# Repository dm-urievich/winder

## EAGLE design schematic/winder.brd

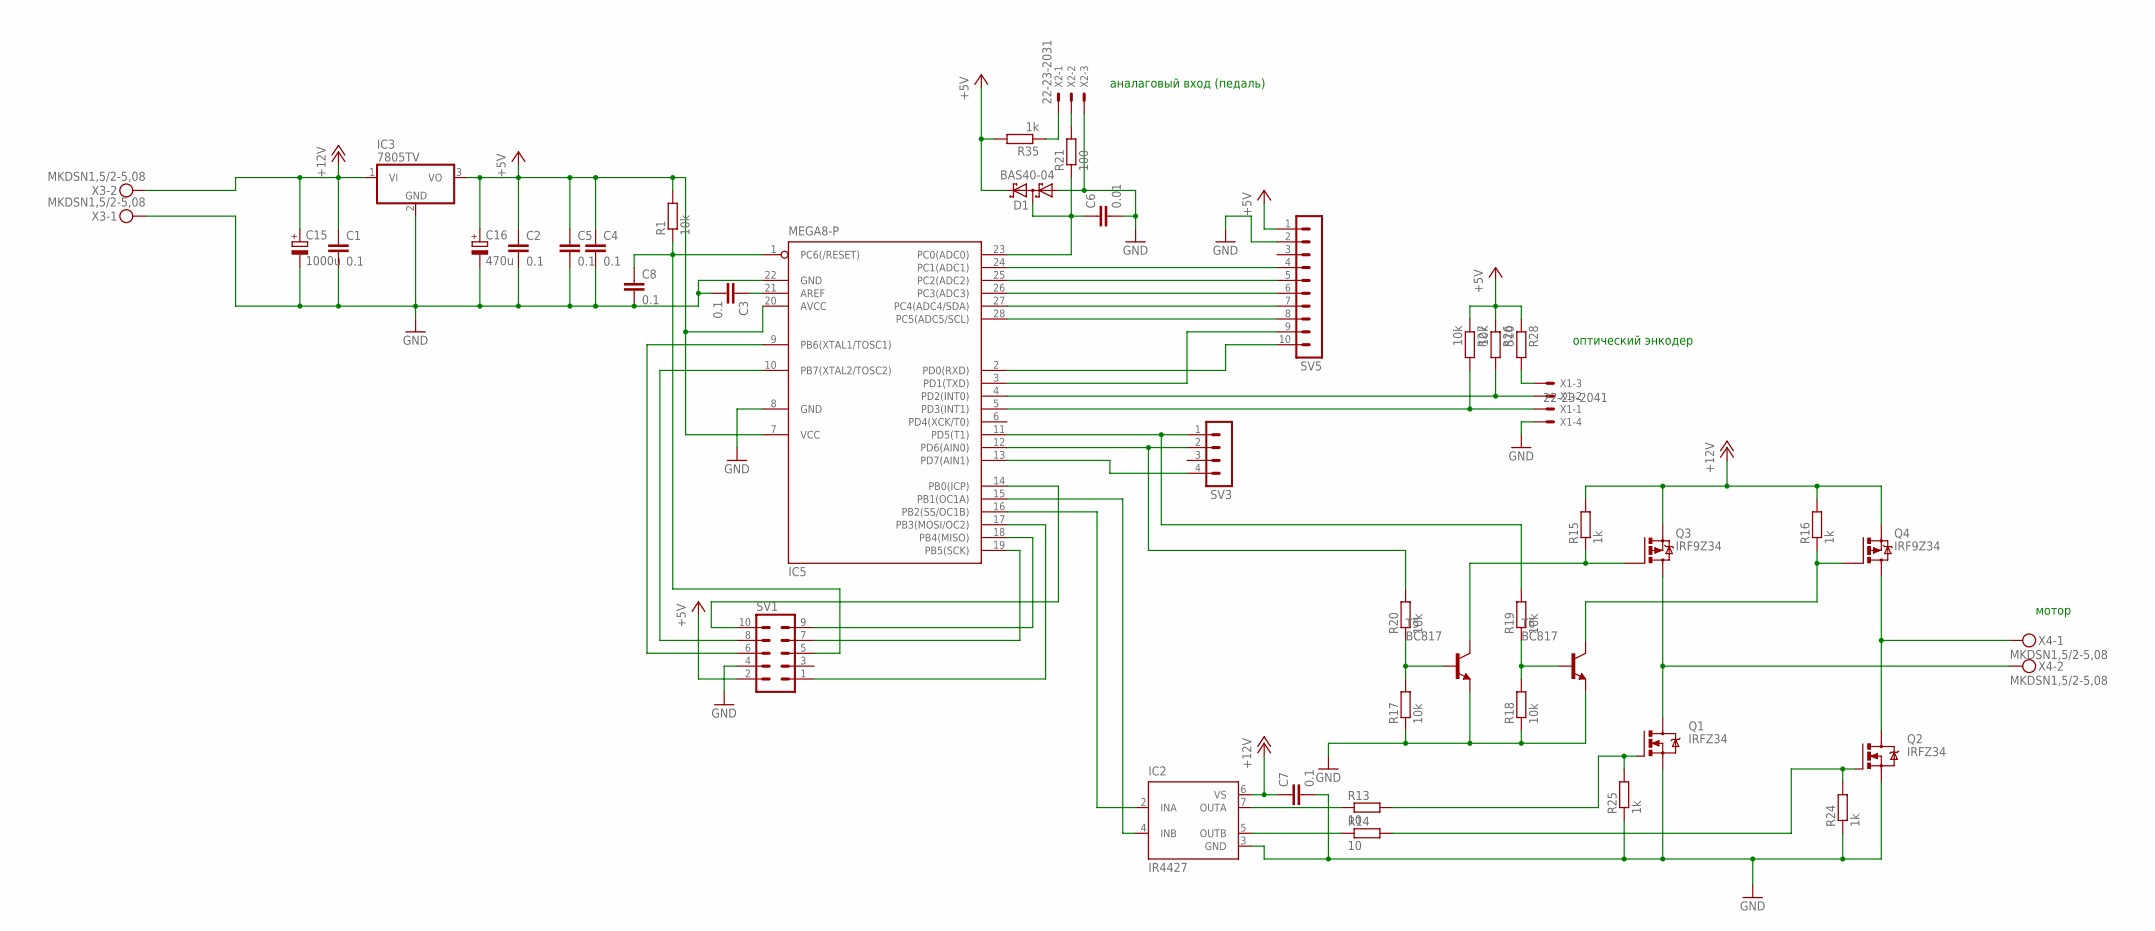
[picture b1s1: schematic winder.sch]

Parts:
C1, C2, C3, C4, C5, C7, C8: 0.1; C0805
C6: 0.01; C0805
C15: 1000u; E3,5-10
C16: 470u; E3,5-10
D1: BAS40-04; SOT23
IC2: IR4427; DIL08
IC3: 7805TV; TO220V
IC5: MEGA8-P; DIL28-3
Q1, Q2: IRFZ34; TO220BV
Q3, Q4: IRF9Z34; TO220BV
R1, R17, R18, R19, R20, R26, R27: 10k; R0805
R13, R14: 10; R0805
R15, R16, R24, R25, R35: 1k; R0805
R21: 100; R0805
R28: 510; R0805
SV1: ML10
SV3: MA04-1
SV5: MA10-1
T5, T6: BC817; SOT23-BEC
X1: 22-23-2041
X2: 22-23-2031
X3, X4: MKDSN1,5/2-5,08

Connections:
+5V: C2.1, C4.1, C5.1, C16.+, D1.2 (C2), IC3.3 (VO), IC5.7 (VCC), IC5.20 (AVCC), R1.2, R26.1, R27.1, R28.1, R35.2, SV1.2, SV5.1
+12V: C1.1, C7.1, C15.+, IC2.6 (VS), IC3.1 (VI), Q3.S, Q4.S, R15.2, R16.2, X3.2
GND: C1.2, C2.2, C3.2, C4.2, C5.2, C6.2, C7.2, C8.2, C15.-, C16.-, D1.1 (A1), IC2.3 (GND), IC3.2 (GND), IC5.8 (GND), IC5.22 (GND), Q1.S, Q2.S, R17.1, R18.1, R24.1, R25.1, SV1.4, SV5.2, T5.E, T6.E, X1.4, X2.3, X3.1
unnamed: IC5.13 (PD7(AIN1)), SV3.4
unnamed: R28.2, X1.3
unnamed: C6.1, D1.3 (C1A2), IC5.23 (PC0(ADC0)), R21.1
unnamed: IC5.14 (PB0(ICP)), SV1.10
unnamed: IC5.5 (PD3(INT1)), R27.2, X1.1
unnamed: IC5.4 (PD2(INT0)), R26.2, X1.2
unnamed: IC5.28 (PC5(ADC5/SCL)), SV5.8
unnamed: IC5.27 (PC4(ADC4/SDA)), SV5.7
unnamed: Q4.G, R16.1, T6.C
unnamed: Q3.G, R15.1, T5.C
unnamed: R17.2, R20.1, T5.B
unnamed: R18.2, R19.1, T6.B
unnamed: R21.2, X2.2
unnamed: Q1.D, Q3.D, X4.2
unnamed: Q2.D, Q4.D, X4.1
unnamed: Q1.G, R13.2, R25.2
unnamed: Q2.G, R14.2, R24.2
unnamed: IC2.7 (OUTA), R13.1
unnamed: IC2.5 (OUTB), R14.1
unnamed: IC2.4 (INB), IC5.15 (PB1(OC1A))
unnamed: IC5.10 (PB7(XTAL2/TOSC2)), SV1.8
unnamed: IC5.17 (PB3(MOSI/OC2)), SV1.1
unnamed: C8.1, IC5.1 (PC6(/RESET)), R1.1, SV1.5
unnamed: R35.1, X2.1
unnamed: IC5.19 (PB5(SCK)), SV1.7
unnamed: IC5.18 (PB4(MISO)), SV1.9
unnamed: C3.1, IC5.21 (AREF)
unnamed: IC5.11 (PD5(T1)), R19.2, SV3.1
unnamed: IC5.12 (PD6(AIN0)), R20.2, SV3.2
unnamed: IC5.26 (PC3(ADC3)), SV5.6
unnamed: IC5.25 (PC2(ADC2)), SV5.5
unnamed: IC5.3 (PD1(TXD)), SV5.9
unnamed: IC5.9 (PB6(XTAL1/TOSC1)), SV1.6
unnamed: IC5.2 (PD0(RXD)), SV5.10
unnamed: IC5.24 (PC1(ADC1)), SV5.4
unnamed: IC2.2 (INA), IC5.16 (PB2(SS/OC1B))

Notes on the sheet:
оптический энкодер
аналаговый вход (педаль)
мотор

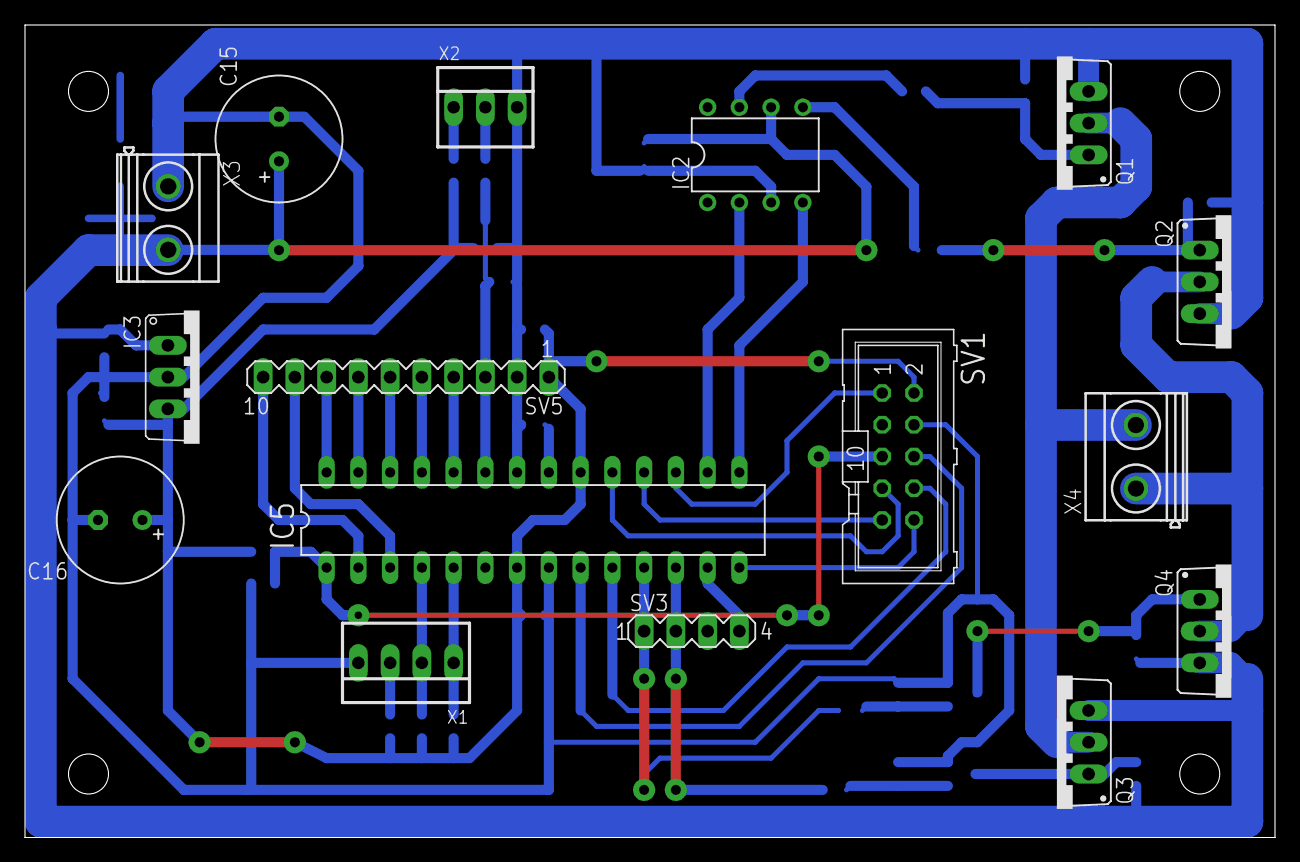
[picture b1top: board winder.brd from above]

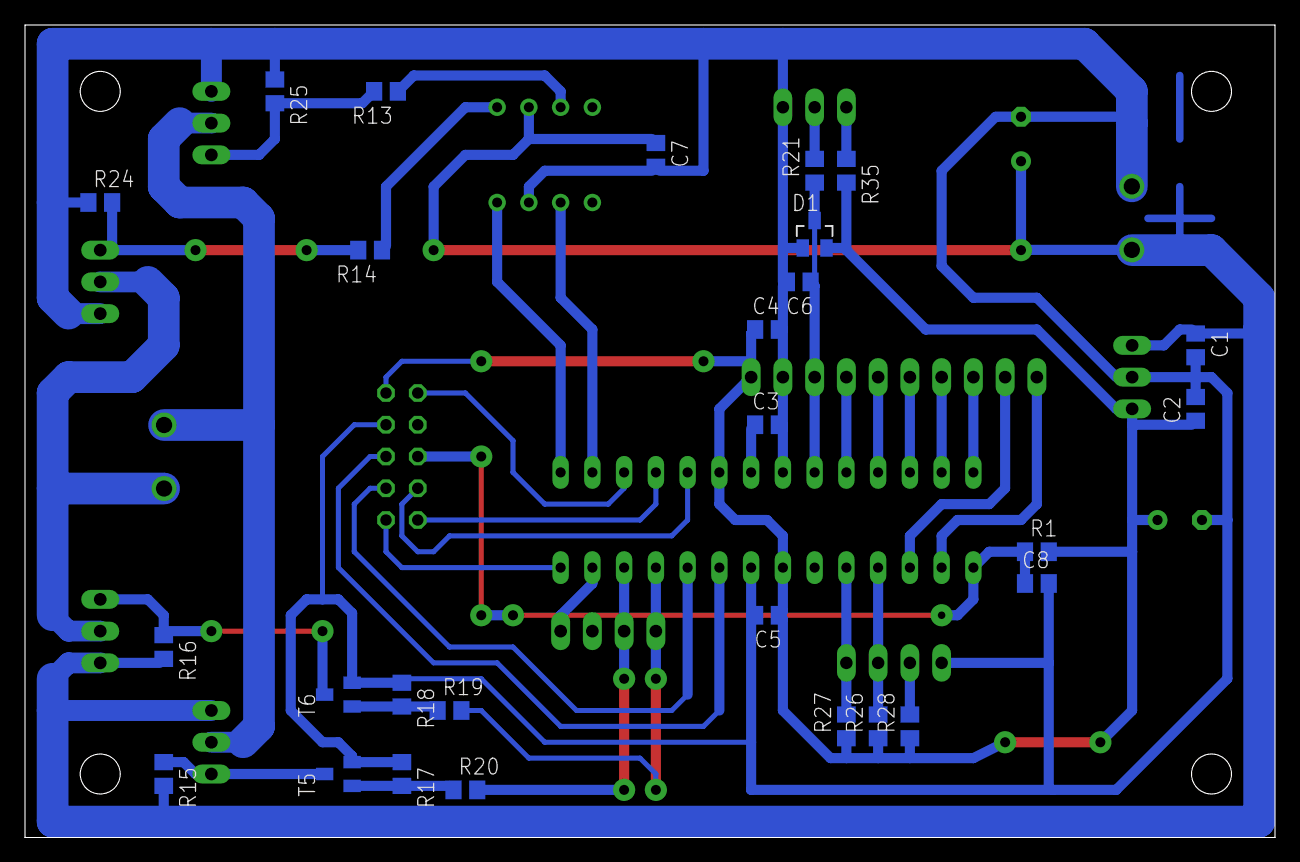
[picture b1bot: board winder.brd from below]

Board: 2 copper layers, 100.0 x 65.0 mm, 43 parts (27 on the bottom side), 39 nets.

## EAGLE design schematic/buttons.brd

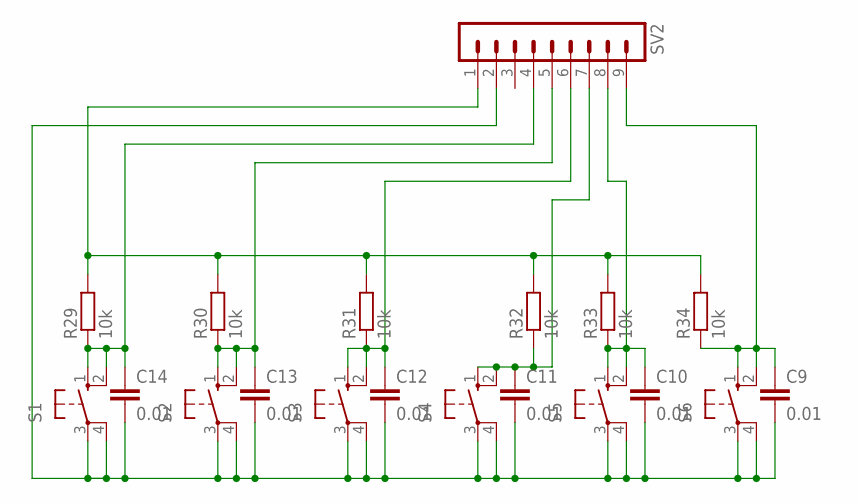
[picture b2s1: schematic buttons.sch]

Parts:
C9, C10, C11, C12, C13, C14: 0.01; C0805
R29, R30, R31, R32, R33, R34: 10k; R0805
S1, S2, S3, S4, S5, S6: 40-XX; B3F-40XX
SV2: MA09-1

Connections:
unnamed: C13.1, R30.1, S2.1 (S), S2.2 (S1), SV2.5
unnamed: C11.1, R32.1, S4.1 (S), S4.2 (S1), SV2.7
unnamed: C10.1, R33.1, S5.1 (S), S5.2 (S1), SV2.8
unnamed: C14.1, R29.1, S1.1 (S), S1.2 (S1), SV2.4
unnamed: C9.1, R34.1, S6.1 (S), S6.2 (S1), SV2.9
unnamed: R29.2, R30.2, R31.2, R32.2, R33.2, R34.2, SV2.1
unnamed: C9.2, C10.2, C11.2, C12.2, C13.2, C14.2, S1.3, S1.4 (P1), S2.3, S2.4 (P1), S3.3, S3.4 (P1), S4.3, S4.4 (P1), S5.3, S5.4 (P1), S6.3, S6.4 (P1), SV2.2
unnamed: C12.1, R31.1, S3.1 (S), S3.2 (S1), SV2.6

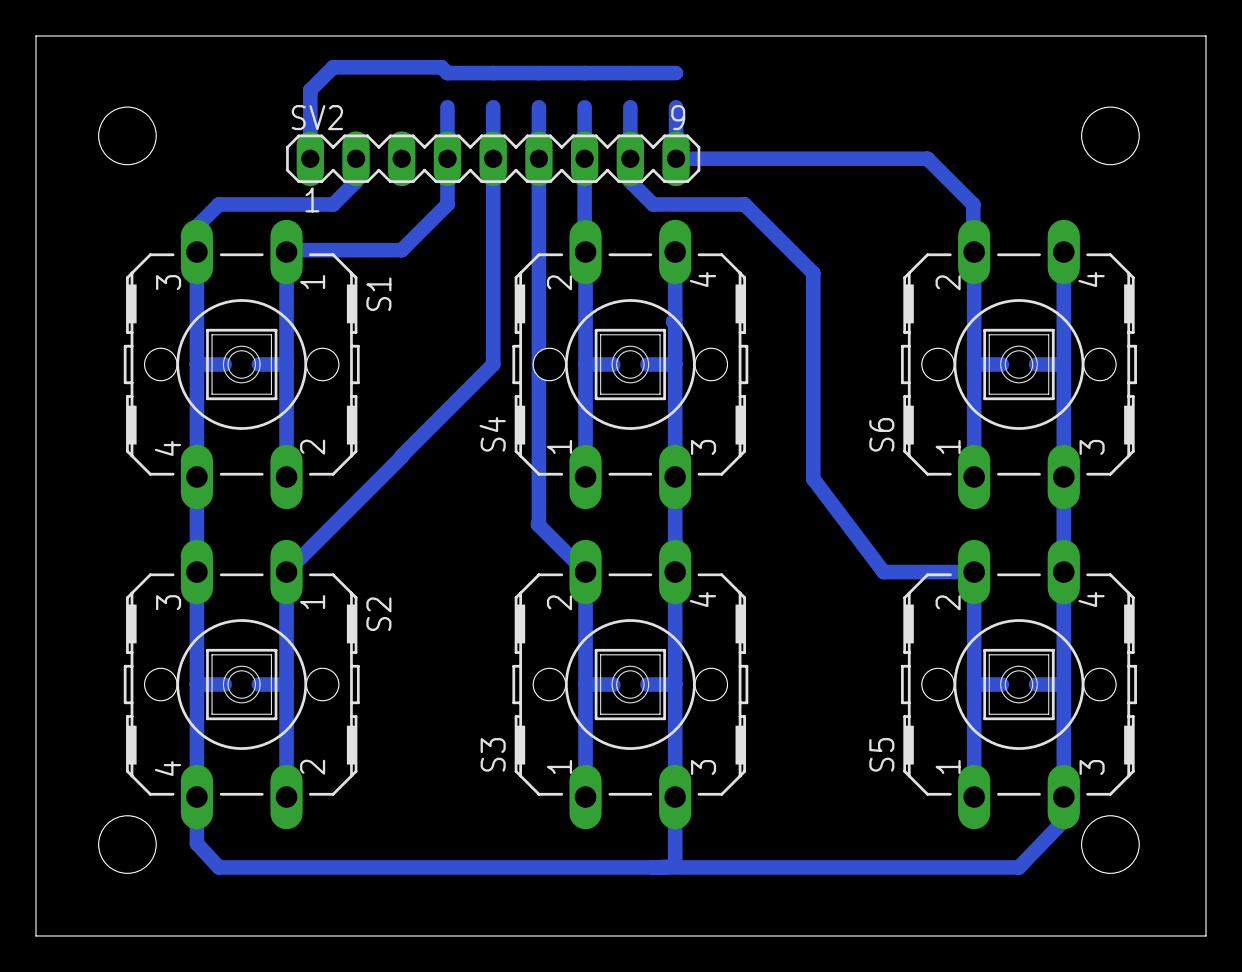
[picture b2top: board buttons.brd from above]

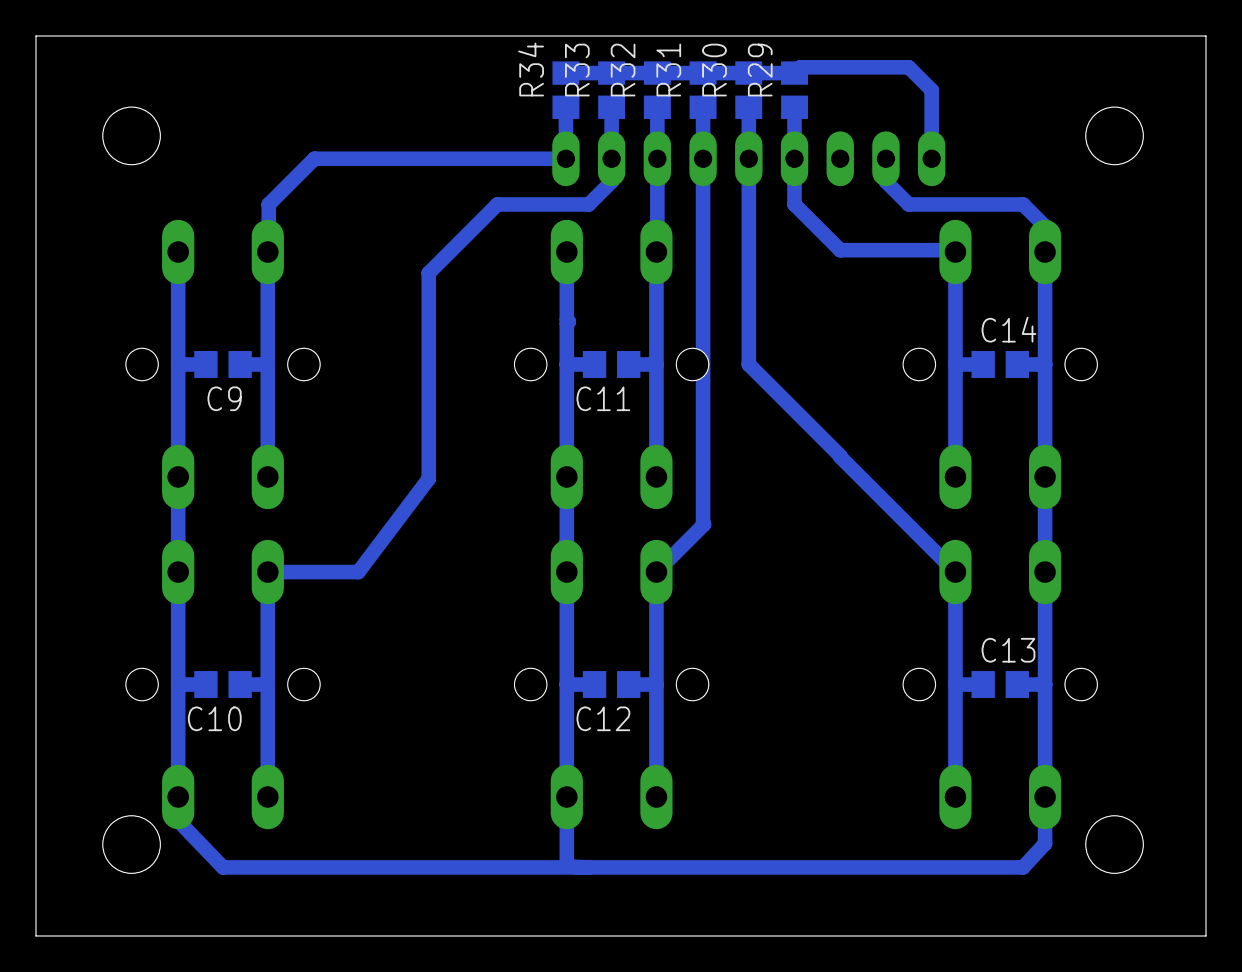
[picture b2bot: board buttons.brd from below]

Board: 2 copper layers, 65.0 x 50.0 mm, 19 parts (12 on the bottom side), 8 nets.

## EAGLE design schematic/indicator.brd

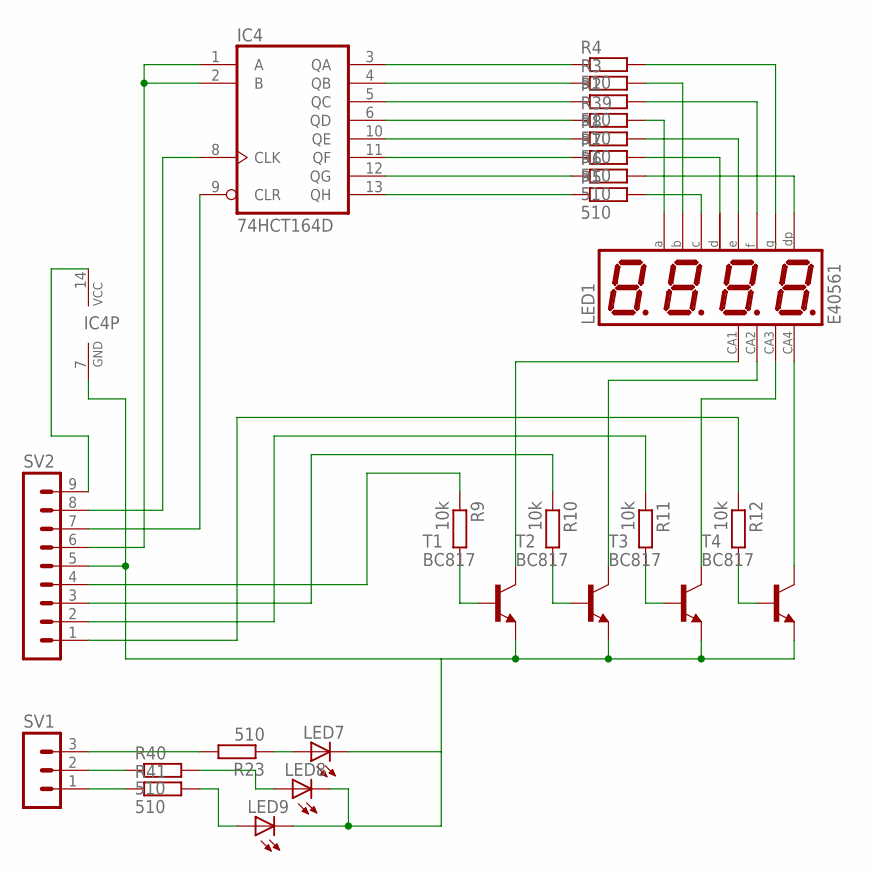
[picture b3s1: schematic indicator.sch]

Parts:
IC4: 74HCT164D; SO14
LED1: E40561; BX56-12
LED7, LED8, LED9: LED5MM
R2, R4, R5, R6, R7, R8, R23, R39, R40, R41: 510; R0805
R3: R-EU_R0805; R0805
R9, R10, R11, R12: 10k; R0805
SV1: MA03-1
SV2: MA09-1
T1, T2, T3, T4: BC817; SOT23-BEC

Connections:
unnamed: R9.2, T1.B
unnamed: R10.2, T2.B
unnamed: R11.2, T3.B
unnamed: R12.2, T4.B
unnamed: LED1.6 (CA), T4.C
unnamed: LED1.8 (CA), T3.C
unnamed: LED1.9 (CA), T2.C
unnamed: LED1.12 (CA), T1.C
unnamed: R40.1, SV1.2
unnamed: LED1.1 (E), R8.2
unnamed: IC4.6 (QD), R39.1
unnamed: IC4.5 (QC), R2.1
unnamed: IC4.4 (QB), R3.1
unnamed: IC4.3 (QA), R4.1
unnamed: IC4.10 (QE), R8.1
unnamed: IC4.11 (QF), R7.1
unnamed: LED1.2 (D), R7.2
unnamed: LED1.3 (DP), R6.2
unnamed: LED1.4 (C), R5.2
unnamed: LED1.5 (G), R4.2
unnamed: LED1.7 (B), R3.2
unnamed: LED1.10 (F), R2.2
unnamed: LED1.11 (A), R39.2
unnamed: R41.1, SV1.1
unnamed: IC4.12 (QG), R6.1
unnamed: R12.1, SV2.1
unnamed: IC4.13 (QH), R5.1
unnamed: IC4.8 (CLK), SV2.8
unnamed: IC4.9 (CLR), SV2.7
unnamed: IC4.7 (GND), LED7.K (C), LED8.K (C), LED9.K (C), SV2.5, T1.E, T2.E, T3.E, T4.E
unnamed: LED7.A, R23.1
unnamed: IC4.1 (A), IC4.2 (B), SV2.6
unnamed: LED8.A, R40.2
unnamed: LED9.A, R41.2
unnamed: R10.1, SV2.3
unnamed: R9.1, SV2.4
unnamed: R11.1, SV2.2
unnamed: IC4.14 (VCC), SV2.9
unnamed: R23.2, SV1.3

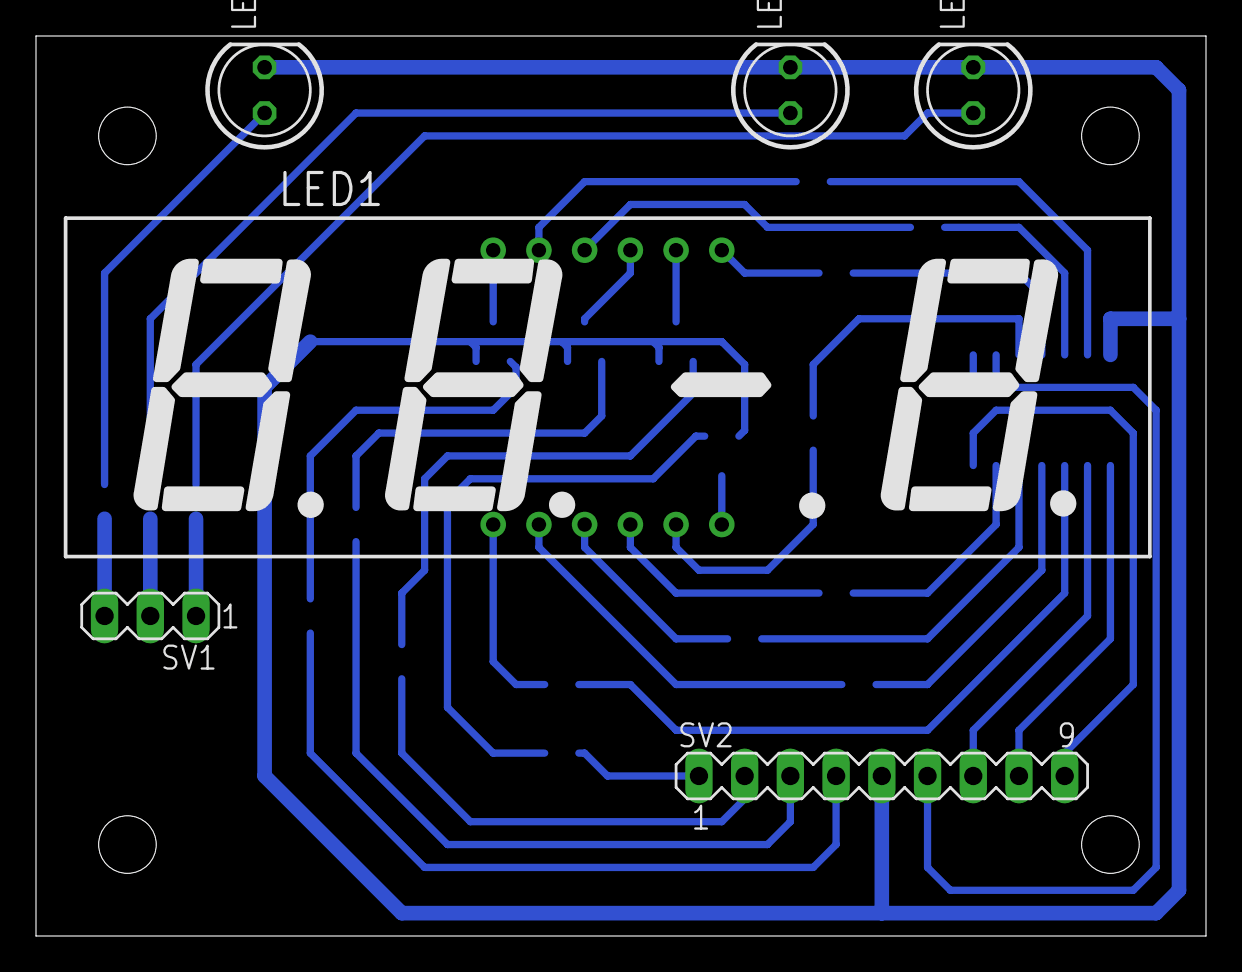
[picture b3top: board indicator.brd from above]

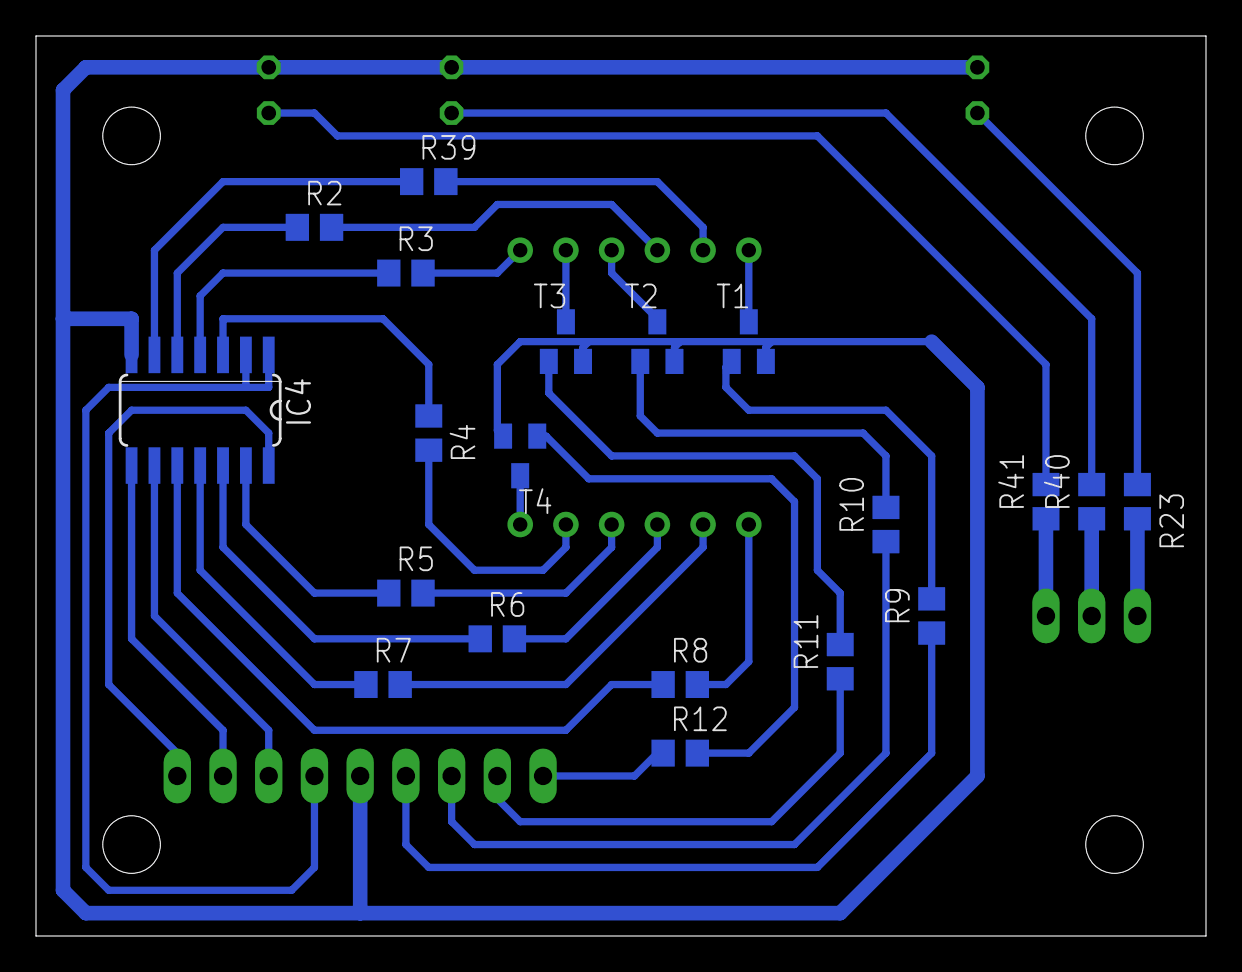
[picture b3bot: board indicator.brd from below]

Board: 2 copper layers, 65.0 x 50.0 mm, 26 parts (20 on the bottom side), 39 nets.

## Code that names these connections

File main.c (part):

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 * сохранять в еепром значение скорости, последнее количество витков, направление вращения
 *
 * подключение:
 * PC0 - ADC, задание скорости
 *
 * PC1 - данные сдвигового регистра
 * PC2 - тактовые импульсы сдвигового регистра
 * PC3 - сброс сдвигового регистра
 *
 * PC4 - светодиод
 * PC5 - светодиод
 *
 * PD0-PD3 катоды индикатора
 * PD0 - 4
 * PD1 - 3
 * PD2 - 2
 * PD3 - 1
 *
 * PD4, PD5 направление вращения
 *
 * PD6, PD7 энкодер
 *
 * PB1, PB2 скорость вращения, ШИМ
 *
 * PB0, PB3-PB7 кнопки
 *
 * функциональные блоки в ПО:
 * кнопки
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
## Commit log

2015-10-06 1st version
2015-10-11 add schematic
2015-10-11 saving settings to eeprom, encoder already works, indicator bugfix
2015-10-11 formatted code, add return to menu in START state (don't tested)
2015-10-11 add full schematic in one sheet
2015-11-08 updtate when write to EEPROM instead write
2015-11-08 second version, fix bug with editing speed end env_value in STOP, fix bug with reverse rotation, rework indication
2016-02-27 add photo device
